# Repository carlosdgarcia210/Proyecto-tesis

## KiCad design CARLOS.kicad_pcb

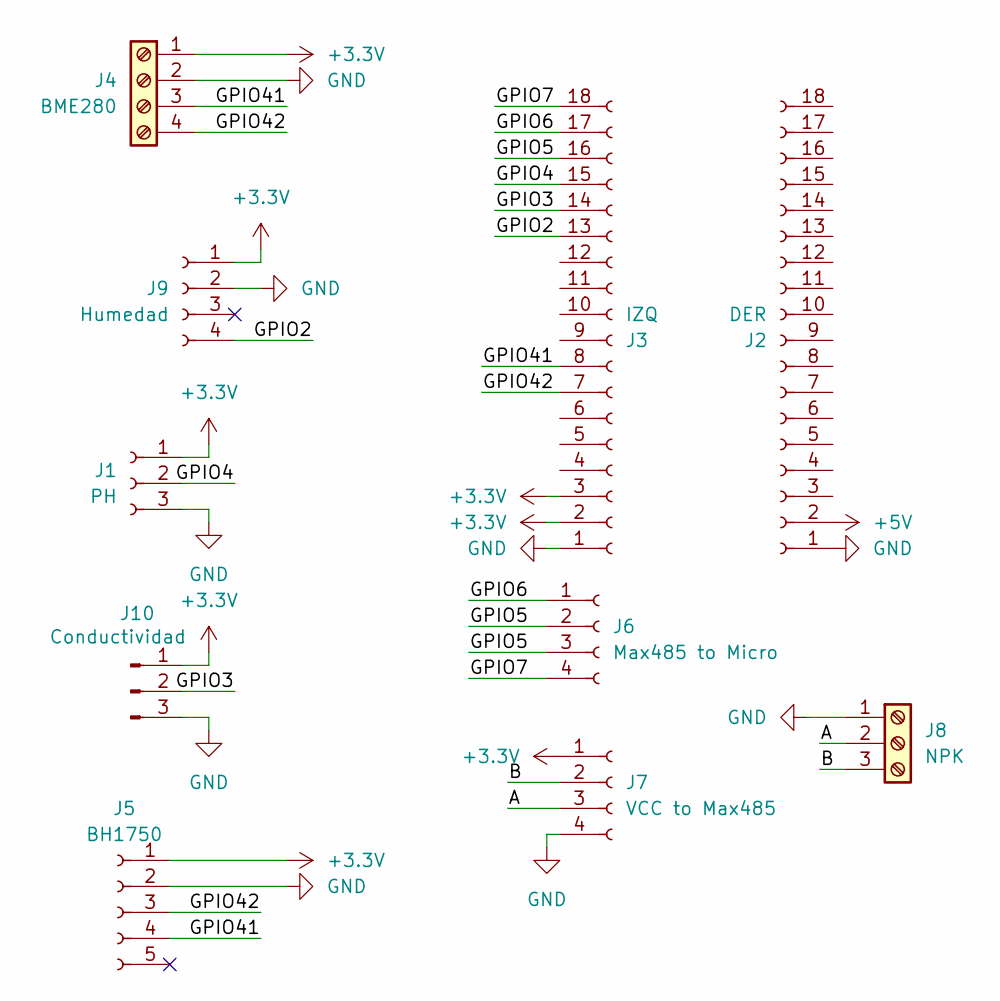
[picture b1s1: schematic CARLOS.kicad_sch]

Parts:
J1: PH; PinSocket_1x03_P2.54mm_Vertical
J2: DER; PinSocket_1x18_P2.54mm_Vertical
J3: IZQ; PinSocket_1x18_P2.54mm_Vertical
J4: BME280; TerminalBlock_MetzConnect_Type055_RT01504HDWU_1x04_P5.00mm_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
J5: BH1750; PinHeader_1x05_P2.54mm_Vertical
J6: Max485 to Micro; PinSocket_1x04_P2.54mm_Vertical
J7: VCC to Max485; PinSocket_1x04_P2.54mm_Vertical
J8: NPK; TerminalBlock_MetzConnect_Type055_RT01503HDWU_1x03_P5.00mm_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
J9: Humedad; PinSocket_1x04_P2.54mm_Vertical
J10: Conductividad; PinHeader_1x03_P2.54mm_Vertical

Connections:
+3.3V: J1.1, J3.2, J3.3, J4.1, J5.1, J7.1, J9.1, J10.1
+5V: J2.2
/A: J7.3, J8.2
/B: J7.2, J8.3
/GPIO2: J3.13, J9.4
/GPIO3: J3.14, J10.2
/GPIO4: J1.2, J3.15
/GPIO5: J3.16, J6.2, J6.3
/GPIO6: J3.17, J6.1
/GPIO7: J3.18, J6.4
/GPIO41: J3.8, J4.3, J5.4
/GPIO42: J3.7, J4.4, J5.3
GND: J1.3, J2.1, J3.1, J4.2, J5.2, J7.4, J8.1, J9.2, J10.3

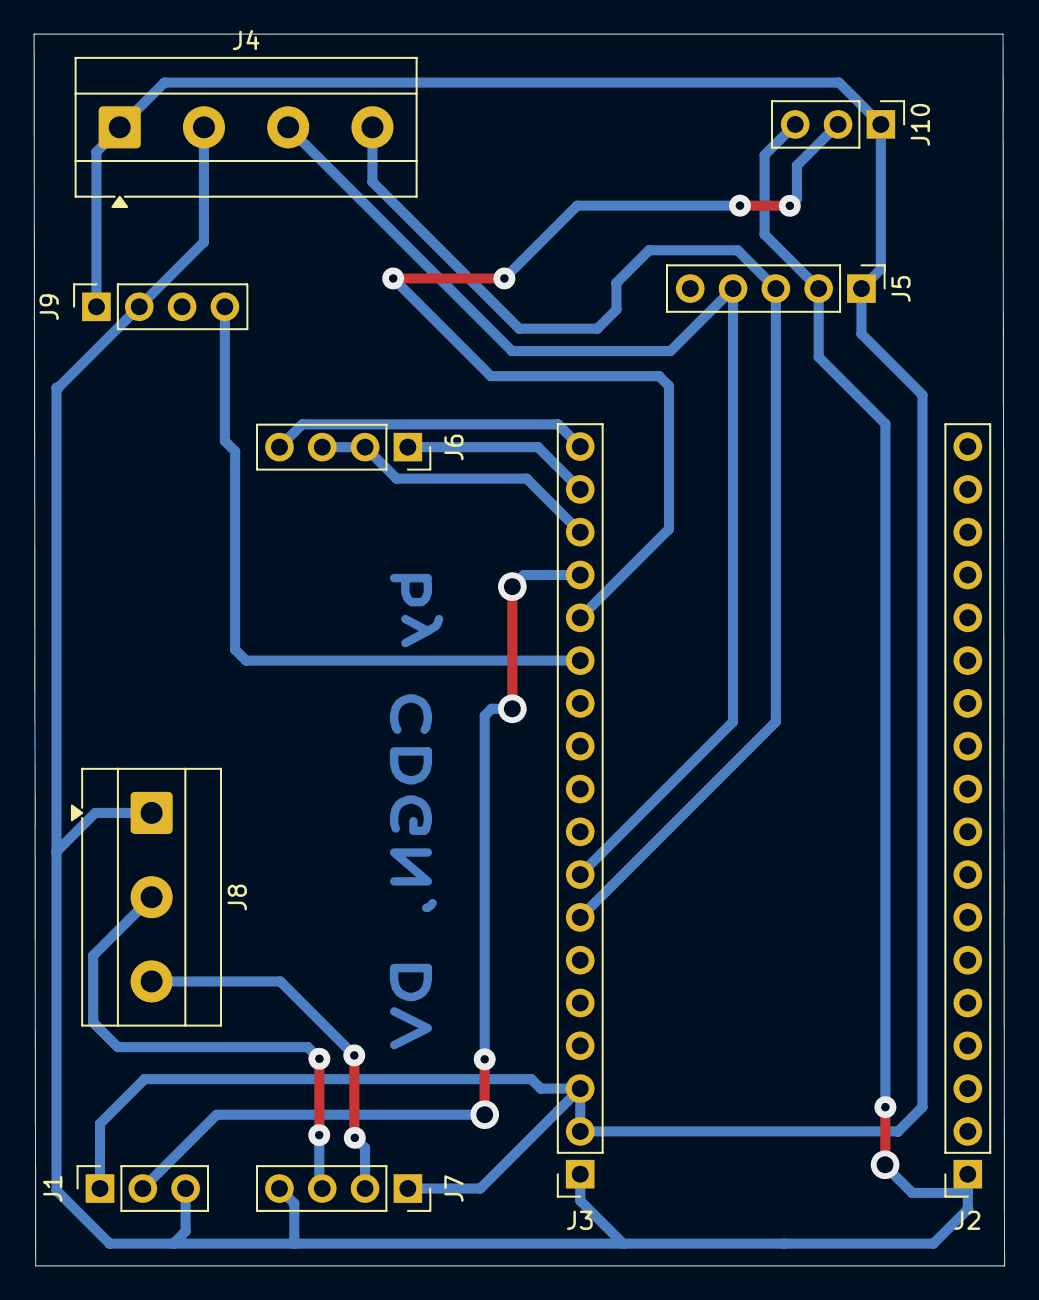
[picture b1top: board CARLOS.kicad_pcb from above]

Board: 2 copper layers, 57.6 x 73.1 mm, 10 parts (0 on the bottom side), 12 nets.
